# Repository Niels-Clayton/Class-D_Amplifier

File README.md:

# [D-Class Amplifier](https://niels-clayton.github.io/D-Class_Amplifier/)
ECEN405 Class-D amplifier group project

**Team members:**

- Daniel Eisen
- Nickolai Wolfe
- Niels Clayton

---
## Input Filter Stage

- The input stage will use two active filters, a 10Hz corner frequency high pass filter, and a 200Hz corner frequency low pass filter. This will provide an overall filter passband of 10Hz - 200Hz.

---
## S-PWM Generation

- It is important to be able to effectively filter out the switching frequency of the sinusoidal pulse width modulated (SPWM) signal output. because of this, we want to ensure that the switching frequency is at least two decades above the maximum output frequency. This will ensure an attenuation of at least 40dB of the switching noise by the output filter.

- Our output frequency range is 10Hz - 200Hz. To achieve the required attenuation of the switching frequency, it will nee to be 20kHz.

---
## Power Stage
- 2x IR21834PBF drivers
  - V_offset: 600V max
  - I_o+-: 1.4A/1.8A
  - T_on/off: 180ns/220ns
  - MT: 35ns
  - V_cc: 10-20V (single)
  - V_in: Vss+5V
- 4x PHP23NQ11T,127 Fets
  - minimum BV_dss of 45V
  - Actual: 110V
  - Gate Charge Qg: 10nC
  - Rdson: 49m 

https://www.infineon.com/dgdl/Infineon-Using_Monolithic_Voltage_Gate_Drivers-AN-v01_00-EN.pdf?fileId=5546d462584d1d4a01585242c11947b1
---
## Output filter
Signal freq max of 200Hz, Switching frequency of ~25kHz
Place corner frequency of filter at 2kHz (decade centred)
mes

https://datasheets.maximintegrated.com/en/ds/MAX4295.pdf

Figure 4c. Alternate Balanced 2-Pole Filter

Balanced 2-Pole (Figure 4b):
A  balanced  2-pole  filter  does  not  have  the  common-
mode swing problem of the single-ended filter.
C = 2 / (√2 ✕ RL ✕ ωo), L = (√2 ✕ RL)/(2 ✕ ωo); choosing
fo =  30kHz  and  RL =  4Ω,  C1a  =  C1b  =  2.0μF,  L1a  =
L1b = 15μH.
A single capacitor connected across RL, with a value of
CL = 1/(√2 ✕ RL ✕ ωo), can be used in place of C1a and
C1b.  However,  the  configuration  as  shown  gives  an
improved  rejection  to  common-mode  signal  compo-
nents  of  OUT+_  and  OUT-_.    If  the  single  capacitor
scheme is used, additional capacitors (Ca and Cb) can
be  added  from  each  side  of  RL,  providing  a  high-fre-
quency  short  to  ground  (Figure  4c).  These  capacitors
should be approximately 0.2 ✕ CL.

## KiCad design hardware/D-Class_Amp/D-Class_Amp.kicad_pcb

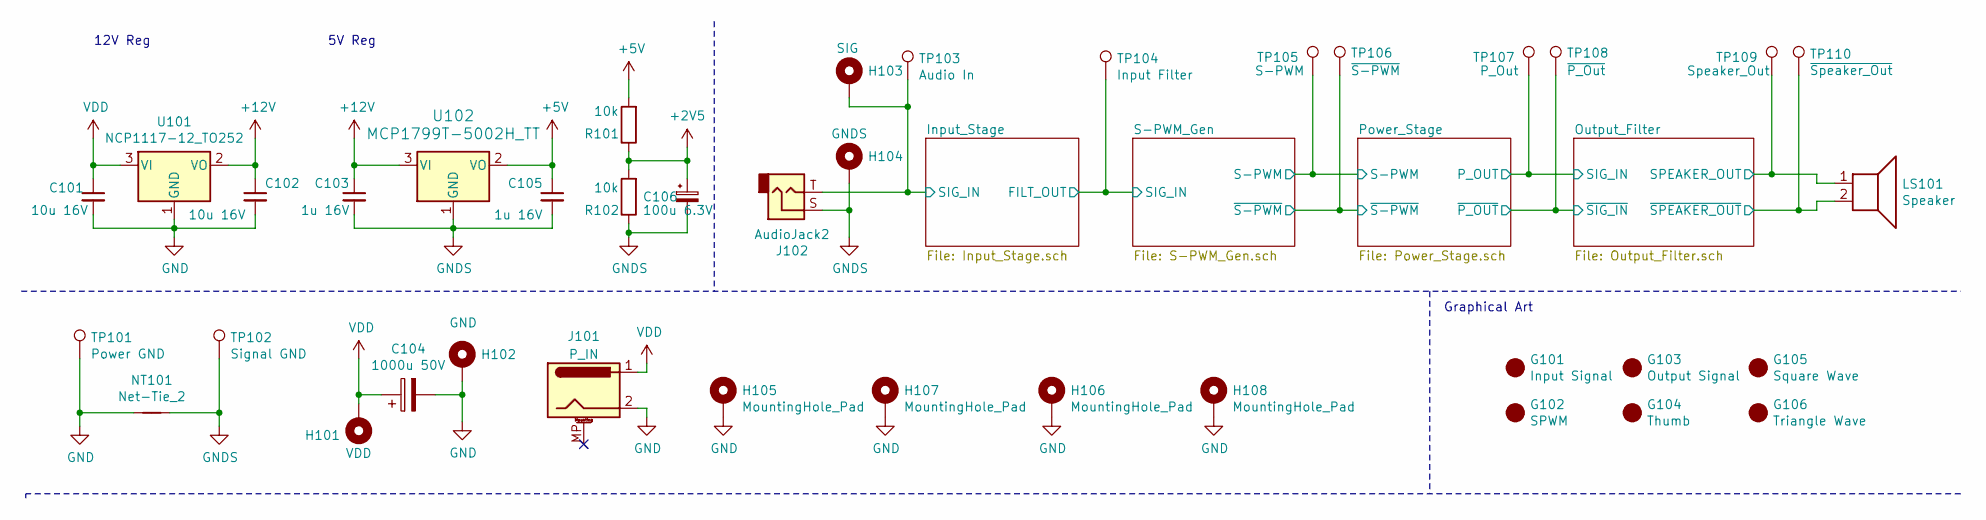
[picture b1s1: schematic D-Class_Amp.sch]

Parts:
C101, C102: 10u 16V; C_0805_2012Metric_Pad1.18x1.45mm_HandSolder; Part Number CL21A106KOQNNWE; DigiKey Price 0.34
C103, C105: 1u 16V; C_0805_2012Metric_Pad1.18x1.45mm_HandSolder; Part Number 885012207051; DigiKey Price 0.16
C104: 1000u 50V; CP_Radial_D10.0mm_P5.00mm; Part Number UVR1H102MHD1TO; DigiKey Price 1
C106: 100u 6.3V; CP_Elec_4x5.4; Part Number 885012207051; DigiKey Price 0.16
G101: Input Signal; sine
G102: SPWM
G103: Output Signal; sine
G104: Thumb; thumb
G105: Square Wave; square
G106: Triangle Wave; triangle
H101: VDD; MountingHole_3mm_Pad_Via
H102: GND; MountingHole_3mm_Pad_Via
H103: SIG; MountingHole_3mm_Pad_Via
H104: GNDS; MountingHole_3mm_Pad_Via
H105, H106, H107, H108: MountingHole_Pad; MountingHole_3.2mm_M3_ISO14580_Pad
J101: P_IN; BarrelJack_Horizontal; Part Number PJ-002BH; DigiKey Price 1.20
J102: AudioJack2; CUI_MJ-63022A; Part Number MJ-63022A; DigiKey Price 2.27
LS101: Speaker
NT101: Net-Tie_2; NetTie-2_SMD_Pad2.0mm
R101, R102: 10k; R_0805_2012Metric_Pad1.20x1.40mm_HandSolder; Part Number RC0805JR-0710KL; DigiKey Price 0.16
TP101: Power GND; TestPoint_THTPad_D1.0mm_Drill0.5mm
TP102: Signal GND; TestPoint_THTPad_D1.0mm_Drill0.5mm
TP103: Audio In; TestPoint_THTPad_D1.0mm_Drill0.5mm
TP104: Input Filter; TestPoint_THTPad_D1.0mm_Drill0.5mm
TP105: S-PWM; TestPoint_THTPad_D1.0mm_Drill0.5mm
TP106: ~S-PWM; TestPoint_THTPad_D1.0mm_Drill0.5mm
TP107: P_Out; TestPoint_THTPad_D1.0mm_Drill0.5mm
TP108: ~P_Out; TestPoint_THTPad_D1.0mm_Drill0.5mm
TP109: Speaker_Out; TestPoint_THTPad_D1.0mm_Drill0.5mm
TP110: ~Speaker_Out; TestPoint_THTPad_D1.0mm_Drill0.5mm
U101: NCP1117-12_TO252; TO-252-2; Part Number NCP1117DT12G; DigiKey Price 1.18
U102: MCP1799T-5002H_TT; SOT-23_Handsoldering; Part Number MCP1799T-5002H/TT; DigiKey Price 0.62

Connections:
+2V5: C106.1, R101.1, R102.2; also elsewhere on the board
+5V: C105.1, R101.2, U102.2 (VO); also elsewhere on the board
+12V: C102.1, C103.1, U101.2 (VO), U102.3 (VI); also elsewhere on the board
/Input_Stage/FILT_OUT: TP104.1; also elsewhere on the board
/Input_Stage/SIG_IN: H103.1, J102.T, TP103.1; also elsewhere on the board
/Output_Filter/SPEAKER_OUT: LS101.1, TP109.1; also elsewhere on the board
/Output_Filter/~SPEAKER_OUT: LS101.2, TP110.1; also elsewhere on the board
/Power_Stage/P_OUT: TP107.1; also elsewhere on the board
/Power_Stage/S-PWM: TP105.1; also elsewhere on the board
/Power_Stage/~P_OUT: TP108.1; also elsewhere on the board
/Power_Stage/~S-PWM: TP106.1; also elsewhere on the board
GND: C101.2, C102.2, C104.2, H102.1, H105.1, H106.1, H107.1, H108.1, J101.2, NT101.1, TP101.1, U101.1 (GND); also elsewhere on the board
GNDS: C103.2, C105.2, C106.2, H104.1, J102.S, NT101.2, R102.1, TP102.1, U102.1 (GND); also elsewhere on the board
VDD: C101.1, C104.1, H101.1, J101.1, U101.3 (VI); also elsewhere on the board

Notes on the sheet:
12V Reg
5V Reg
Graphical Art

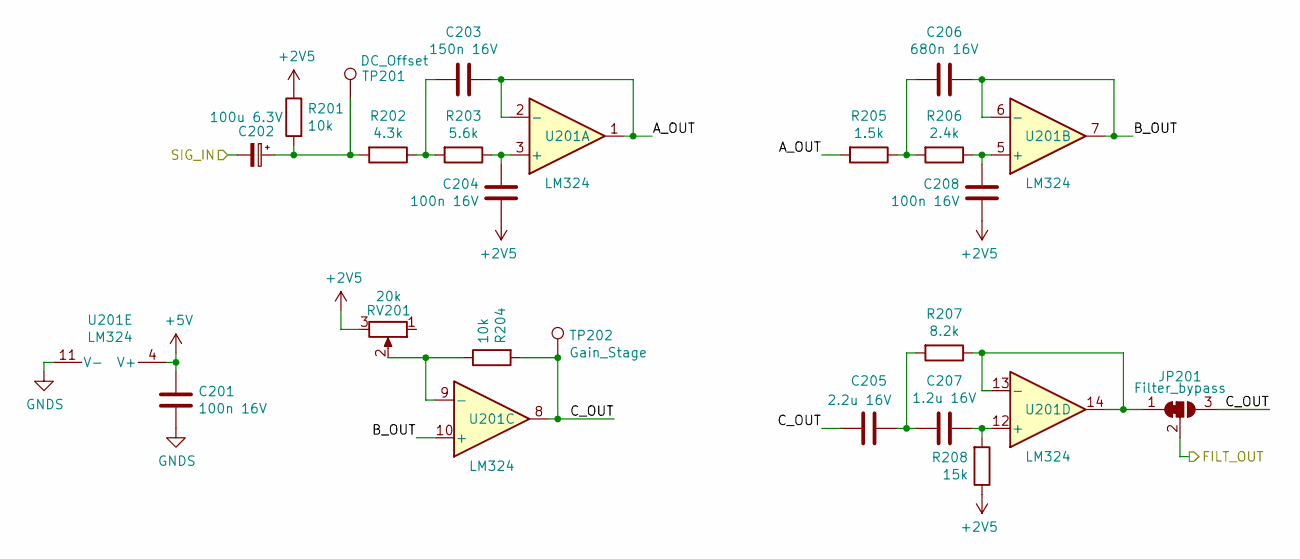
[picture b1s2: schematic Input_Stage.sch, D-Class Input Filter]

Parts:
C201, C204, C208: 100n 16V; C_0805_2012Metric_Pad1.18x1.45mm_HandSolder; Part Number 885012207045; DigiKey Price 0.16
C202: 100u 6.3V; CP_Elec_4x5.4; Part Number 865080142007; DigiKey Price 0.32
C203: 150n 16V; C_0805_2012Metric_Pad1.18x1.45mm_HandSolder; Part Number CL21B154KOANNNC; DigiKey Price 0.16
C205: 2.2u 16V; C_0805_2012Metric_Pad1.18x1.45mm_HandSolder; Part Number L21A225KOFNNNE; DigiKey Price 0.26
C206: 680n 16V; C_0805_2012Metric_Pad1.18x1.45mm_HandSolder; Part Number CL21B684KOFNNNG; DigiKey Price 0.16
C207: 1.2u 16V; C_0805_2012Metric_Pad1.18x1.45mm_HandSolder; Part Number C0805C125K4PAC7800; DigiKey Price 0.67
JP201: Filter_bypass; SolderJumper-3_P1.3mm_Bridged12_RoundedPad1.0x1.5mm_NumberL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
R201, R204: 10k; R_0805_2012Metric_Pad1.20x1.40mm_HandSolder; Part Number RC0805JR-0710KL; DigiKey Price 0.16
R202: 4.3k; R_0805_2012Metric_Pad1.20x1.40mm_HandSolder; Part Number RC0805JR-074K3L; DigiKey Price 0.16
R203: 5.6k; R_0805_2012Metric_Pad1.20x1.40mm_HandSolder; Part Number RC0805JR-075K6L; DigiKey Price 0.16
R205: 1.5k; R_0805_2012Metric_Pad1.20x1.40mm_HandSolder; Part Number CRCW08051K50FKEAC; DigiKey Price 0.16
R206: 2.4k; R_0805_2012Metric_Pad1.20x1.40mm_HandSolder; Part Number ERA-6AED242V; DigiKey Price 0.16
R207: 8.2k; R_0805_2012Metric_Pad1.20x1.40mm_HandSolder; Part Number RC0805JR-078K2L; DigiKey Price 0.16
R208: 15k; R_0805_2012Metric_Pad1.20x1.40mm_HandSolder; Part Number RC0805JR-0715KL; DigiKey Price 0.16
RV201: 20k; Potentiometer_Vishay_T73YP_Vertical; Part Number CT6EP203; DigiKey Price 1.25
TP201: DC_Offset; TestPoint_THTPad_D1.0mm_Drill0.5mm
TP202: Gain_Stage; TestPoint_THTPad_D1.0mm_Drill0.5mm
U201: LM324; SOIC-14_3.9x8.7mm_P1.27mm; Part Number LM324DR; DigiKey Price 0.62

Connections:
+2V5: C204.1, C208.1, R201.1, R208.1, RV201.3; also elsewhere on the board
+5V: C201.1, U201.4 (V+); also elsewhere on the board
/Input_Stage/A_OUT: C203.1, R205.2, U201.1, U201.2 (-)
/Input_Stage/B_OUT: C206.1, U201.6 (-), U201.7, U201.10 (+)
/Input_Stage/C_OUT: C205.2, JP201.3 (B), R204.2, TP202.1, U201.8
/Input_Stage/FILT_OUT: JP201.2 (C); also elsewhere on the board
/Input_Stage/SIG_IN: C202.2; also elsewhere on the board
GNDS: C201.2, U201.11 (V-); also elsewhere on the board
unnamed: C202.1, R201.2, R202.2, TP201.1
unnamed: C203.2, R202.1, R203.2
unnamed: C204.2, R203.1, U201.3 (+)
unnamed: C205.1, C207.2, R207.2
unnamed: C206.2, R205.1, R206.2
unnamed: C207.1, R208.2, U201.12 (+)
unnamed: C208.2, R206.1, U201.5 (+)
unnamed: JP201.1 (A), R207.1, U201.13 (-), U201.14
unnamed: R204.1, RV201.2, U201.9 (-)

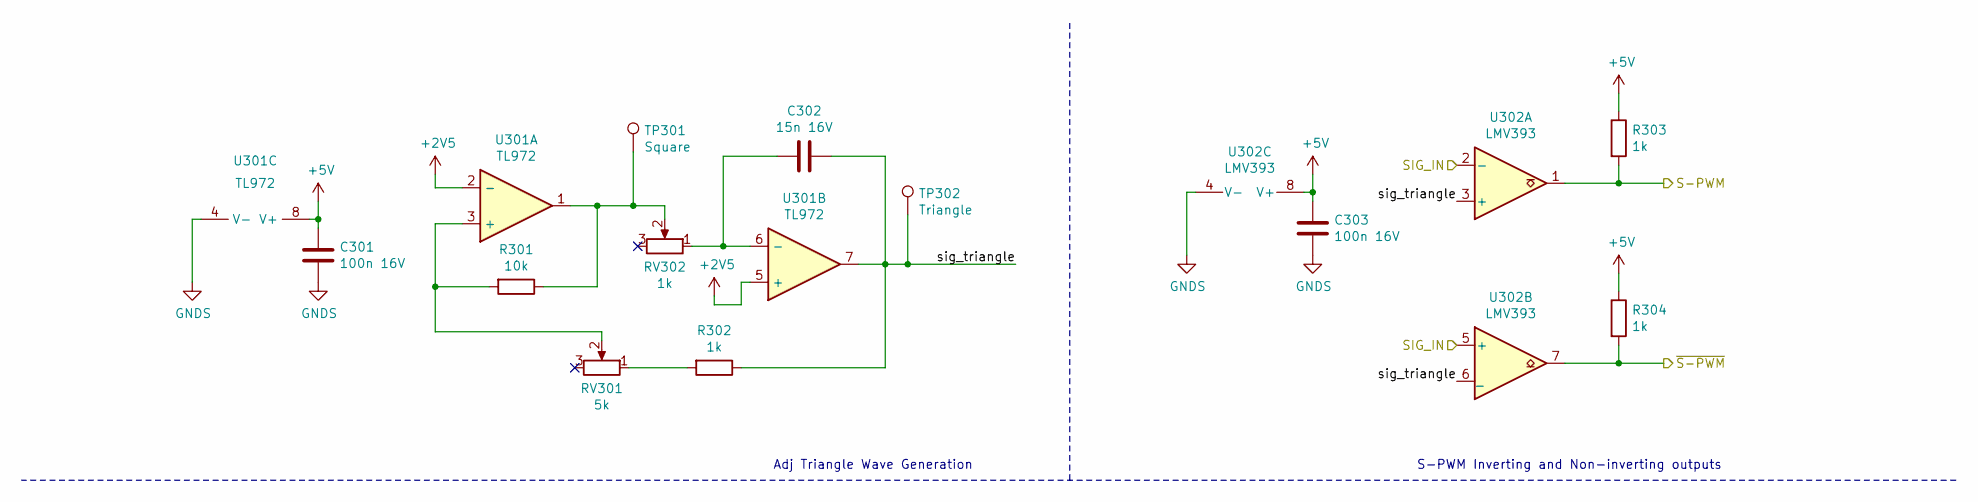
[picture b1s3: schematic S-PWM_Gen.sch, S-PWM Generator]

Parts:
C301, C303: 100n 16V; C_0805_2012Metric_Pad1.18x1.45mm_HandSolder; Part Number 885012207045; DigiKey Price 0.16
C302: 15n 16V; R_0805_2012Metric_Pad1.20x1.40mm_HandSolder; Part Number 885012207040; DigiKey Price 0.16
R301: 10k; R_0805_2012Metric_Pad1.20x1.40mm_HandSolder; Part Number RC0805JR-0710KL; DigiKey Price 0.16
R302, R303, R304: 1k; R_0805_2012Metric_Pad1.20x1.40mm_HandSolder; Part Number RC0805JR-0710KL; DigiKey Price 0.16
RV301: 5k; Potentiometer_Vishay_T73YP_Vertical; Part Number CT6EP502; DigiKey Price 1.25
RV302: 1k; Potentiometer_Vishay_T73YP_Vertical; Part Number CT6EP102; DigiKey Price 1.25
TP301: Square; TestPoint_THTPad_D1.0mm_Drill0.5mm
TP302: Triangle; TestPoint_THTPad_D1.0mm_Drill0.5mm
U301: TL972; SOIC-8_3.9x4.9mm_P1.27mm; Part Number TL972IDR; DigiKey Price 1.47
U302: LMV393; SOIC-8_3.9x4.9mm_P1.27mm; Part Number LMV393S-13; DigiKey Price 0.75

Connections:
+2V5: U301.2 (-), U301.5 (+); also elsewhere on the board
+5V: C301.1, C303.1, R303.1, R304.1, U301.8 (V+), U302.8 (V+); also elsewhere on the board
/Input_Stage/FILT_OUT: U302.2 (-), U302.5 (+); also elsewhere on the board
/Power_Stage/S-PWM: R303.2, U302.1; also elsewhere on the board
/Power_Stage/~S-PWM: R304.2, U302.7; also elsewhere on the board
/S-PWM_Gen/sig_triangle: C302.1, R302.1, TP302.1, U301.7, U302.3 (+), U302.6 (_)
GNDS: C301.2, C303.2, U301.4 (V-), U302.4 (V-); also elsewhere on the board
unnamed: C302.2, RV302.1, U301.6 (-)
unnamed: R301.1, RV302.2, TP301.1, U301.1
unnamed: R301.2, RV301.2, U301.3 (+)
unnamed: R302.2, RV301.1

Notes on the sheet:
Adj Triangle Wave Generation
S-PWM Inverting and Non-inverting outputs

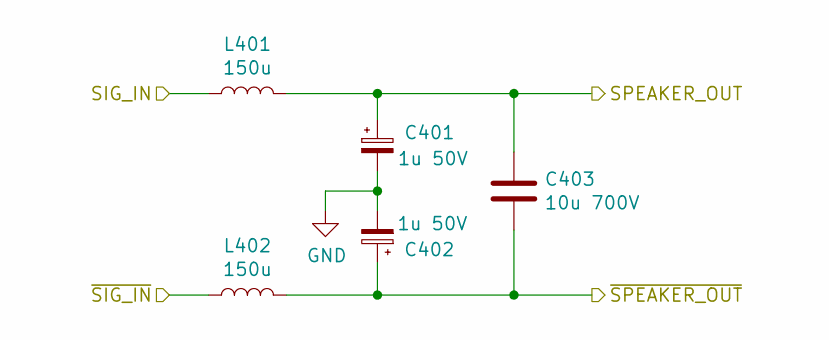
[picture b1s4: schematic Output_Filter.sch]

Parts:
C401, C402: 1u 50V; CP_Elec_4x5.4; Part Number 865080640001; DigiKey Price 0.29
C403: 10u 700V; C4AQJLU5100M19J_film_capacitor; Part Number C4AQJLU5100M19J; DigiKey Price 5.67
L401, L402: 150u; IND_HCTI-150-5.0; Part Number HCTI-150-5.0; DigiKey Price 4.20

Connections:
/Output_Filter/SPEAKER_OUT: C401.1, C403.1, L401.2; also elsewhere on the board
/Output_Filter/~SPEAKER_OUT: C402.1, C403.2, L402.2; also elsewhere on the board
/Power_Stage/P_OUT: L401.1; also elsewhere on the board
/Power_Stage/~P_OUT: L402.1; also elsewhere on the board
GND: C401.2, C402.2; also elsewhere on the board

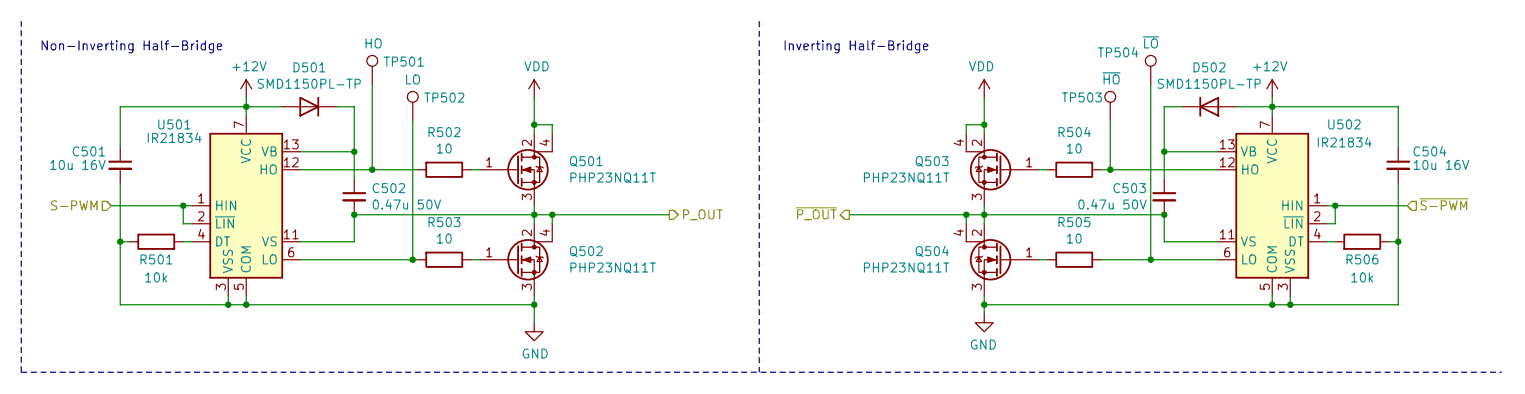
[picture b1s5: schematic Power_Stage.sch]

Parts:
C501, C504: 10u 16V; C_0805_2012Metric_Pad1.18x1.45mm_HandSolder; Part Number CL21A106KOQNNWE; DigiKey Price 0.34
C502, C503: 0.47u 50V; C_0805_2012Metric_Pad1.18x1.45mm_HandSolder; Part Number CL21B474KBFNNNG; DigiKey Price 0.16
D501, D502: SMD1150PL-TP; D_SOD-123F; Part Number UG1B-E3/54; DigiKey Price 0.67
Q501, Q502, Q503, Q504: PHP23NQ11T; Part Number PHP23NQ11T,127; DigiKey Price 1.90
R501, R506: 10k; R_0805_2012Metric_Pad1.20x1.40mm_HandSolder; Part Number RC0805JR-0710KL; DigiKey Price 0.16
R502, R503, R504, R505: 10; R_0805_2012Metric_Pad1.20x1.40mm_HandSolder; Part Number ERJ-6ENF10R0V; DigiKey Price 0.16
TP501: HO; TestPoint_THTPad_D1.0mm_Drill0.5mm
TP502: LO; TestPoint_THTPad_D1.0mm_Drill0.5mm
TP503: ~HO; TestPoint_THTPad_D1.0mm_Drill0.5mm
TP504: ~LO; TestPoint_THTPad_D1.0mm_Drill0.5mm
U501, U502: IR21834; SOIC-14_3.9x8.7mm_P1.27mm; Part Number IR21834SPBFDKR-ND; DigiKey Price 5.87

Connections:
+12V: C501.1, C504.1, D501.2 (A), D502.2 (A), U501.7 (VCC), U502.7 (VCC); also elsewhere on the board
/Power_Stage/P_OUT: C502.2, Q501.3 (S), Q502.2 (D), Q502.4 (D), U501.11 (VS); also elsewhere on the board
/Power_Stage/S-PWM: U501.1 (HIN), U501.2 (~LIN); also elsewhere on the board
/Power_Stage/~P_OUT: C503.2, Q503.3 (S), Q504.2 (D), Q504.4 (D), U502.11 (VS); also elsewhere on the board
/Power_Stage/~S-PWM: U502.1 (HIN), U502.2 (~LIN); also elsewhere on the board
GND: C501.2, C504.2, Q502.3 (S), Q504.3 (S), R501.1, R506.1, U501.3 (VSS), U501.5 (COM), U502.3 (VSS), U502.5 (COM); also elsewhere on the board
unnamed: C502.1, D501.1 (K), U501.13 (VB)
unnamed: C503.1, D502.1 (K), U502.13 (VB)
unnamed: Q501.1 (G), R502.1
unnamed: Q502.1 (G), R503.1
unnamed: Q503.1 (G), R504.1
unnamed: Q504.1 (G), R505.1
unnamed: R501.2, U501.4 (DT)
unnamed: R502.2, TP501.1, U501.12 (HO)
unnamed: R503.2, TP502.1, U501.6 (LO)
unnamed: R504.2, TP503.1, U502.12 (HO)
unnamed: R505.2, TP504.1, U502.6 (LO)
unnamed: R506.2, U502.4 (DT)
VDD: Q501.2 (D), Q501.4 (D), Q503.2 (D), Q503.4 (D); also elsewhere on the board

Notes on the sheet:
Non-Inverting Half-Bridge
Inverting Half-Bridge

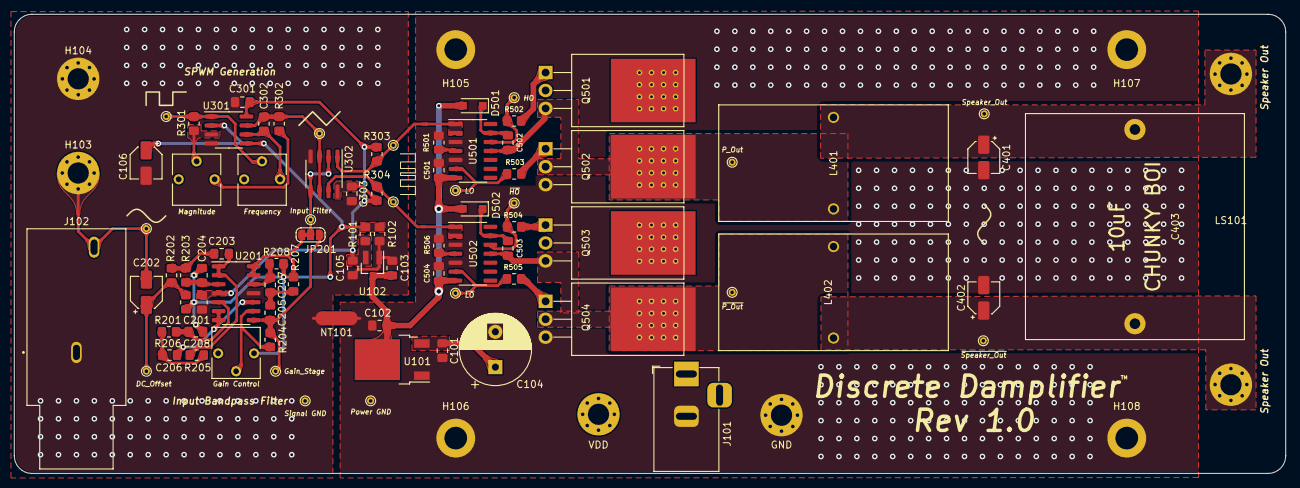
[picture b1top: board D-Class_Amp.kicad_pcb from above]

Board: 2 copper layers, 180.0 x 65.0 mm, 99 parts (1 on the bottom side), 43 nets.

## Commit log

2021-07-21 ligma
2021-07-30 Addid spice simulation file
2021-07-30 added kicad project
2021-07-30 Added Input_Stage sheet and SPICE simulation file.
2021-07-31 all stages genned
2021-07-31 Added documentation directory; built LPF input filter simulation.
2021-07-31 power stage
2021-07-31 driver selection
2021-07-31 Driver key ref
2021-07-31 Created the input filter schematic
2021-07-31 fet specced
2021-07-31 triangle wave generator:
2021-07-31 removed log file
2021-07-31 added parts
2021-07-31 edited input filter ground, created schematic for the SPWM generator
2021-07-31 edits
2021-07-31 Updated input filter spice model.
2021-07-31 grounded man how it work
2021-07-31 Added an input barel jack
2021-07-31 Selected Op-Amp for input stage and labelled parts
2021-07-31 Set footprints for the input stage components.
2021-07-31 updated spice models
2021-07-31 update the letspice model so that the trianlge wave goes from rail to rail. Also added a potentiometer to the feedback path of the triangle wave generator, allowing for precise tuning of this gain.
2021-08-01 Added gain stage to input filter spice simulation
2021-08-01 un-bold the font :)
2021-08-01 Found a cheaper opamp that works good enough
2021-08-01 Changed gain stage's resistors to be E12 series
2021-08-01 layout 1st pass
2021-08-02 anot
2021-08-02 single side
2021-08-02 update potentiometer, add footprints
2021-08-02 deat time and values, 12v reg
2021-08-03 Added input bias circuit and gain stage to input-stage schematic.
2021-08-04 added resistor values
2021-08-04 update the SPW generator to work with a single 5V rail
2021-08-04 foot
2021-08-04 footed ic
2021-08-04 added footprints for opamp
2021-08-04 select comparator and set footprint
2021-08-04 updated the SPWM simulation
2021-08-05 output filter design
2021-08-06 updated input stage schematic
2021-08-08 updated spice sim of SPWM using an array of different opamp models
2021-08-09 filter
2021-08-09 fixed remerge
2021-08-10 output filter comp. TODO real vals
2021-08-10 rebuilt input to match
2021-08-10 added vals oops
2021-08-10 update SPWM sim
2021-08-10 updated SPWM model with new comparators, also added test points to schematic and fixed MOSFET footprints
2021-08-10 Added potentiometer to input gain stage, assigned all input footprints
2021-08-10 Started input stage layout
2021-08-10 added the 5V regulator and updated footprints
2021-08-11 added footprint to 5V reg
2021-08-11 Positioned passives around LM324
2021-08-11 Positioned all passives for the input stage; started trace layout
2021-08-11 updated the Spice sim and added the footprints to the comparator
2021-08-11 supply cap and design notes
2021-08-11 updated fet footprints, and added power stage test points
2021-08-11 re-added supply caps for the gate driver
2021-08-11 Updated input spice model
2021-08-11 Updated the spice simulation again lol teehee
2021-08-11 output sim real val
2021-08-11 Add footprints to the output filter and select output filter components
2021-08-11 lololol input filter hahaha teehee lolool
2021-08-11 Update lib location tobe within the project dir. this allows for project specific libs across systems
2021-08-11 Fixed the input filter spice simulation
2021-08-11 Updated and fixed the input filter schematic
2021-08-11 updated the SPWM spice sim to be able to take the new gain stage audio input
2021-08-11 layed out the phase phucker
2021-08-11 range of options
2021-08-11 added pricing and and part numbers to all components
2021-08-11 Updated input filter layout
2021-08-12 updated the BOM
2021-08-12 Designed the triangle generator PCB layout, and the power switching stage layout
2021-08-12 REGION CITY
2021-08-12 placed and routed all components, fixed the MOSFET footprints, and added all 3D models.
2021-08-13 PCB done POG
2021-08-17 created a bill of materials
2021-09-13 goddam GNDS bck_plane
2021-10-13 update design
2021-10-15 res cap to ref
2021-10-18 teardrop ref cap, regen BOM
2021-10-18 readded art and regen bom
2021-10-18 Revert "teardrop ref cap, regen BOM"
    This reverts commit 41e1c187b9f88871f416da328e72449a335824d4.
2021-10-18 hopefully fixed the repo
2021-10-19 cleaned bars
2021-10-20 rm ground planes from output zone
2021-10-20 update docs
2021-10-20 update endex'
2021-10-20 update final ibom and index
2021-10-20 github pages link on header
2021-10-21 fixed the inout filter gain stage
2021-10-24 testing unloaded
2021-11-04 update pcb and simulations of sampling
2021-11-08 update the simulation
2021-11-15 remove redundant documentation folder
2021-11-15 added graphical symbols, exchanged THT bootstrapping diodes for SMD diodes, updated BOM
2021-11-20 fixed traces extending beyond pads
